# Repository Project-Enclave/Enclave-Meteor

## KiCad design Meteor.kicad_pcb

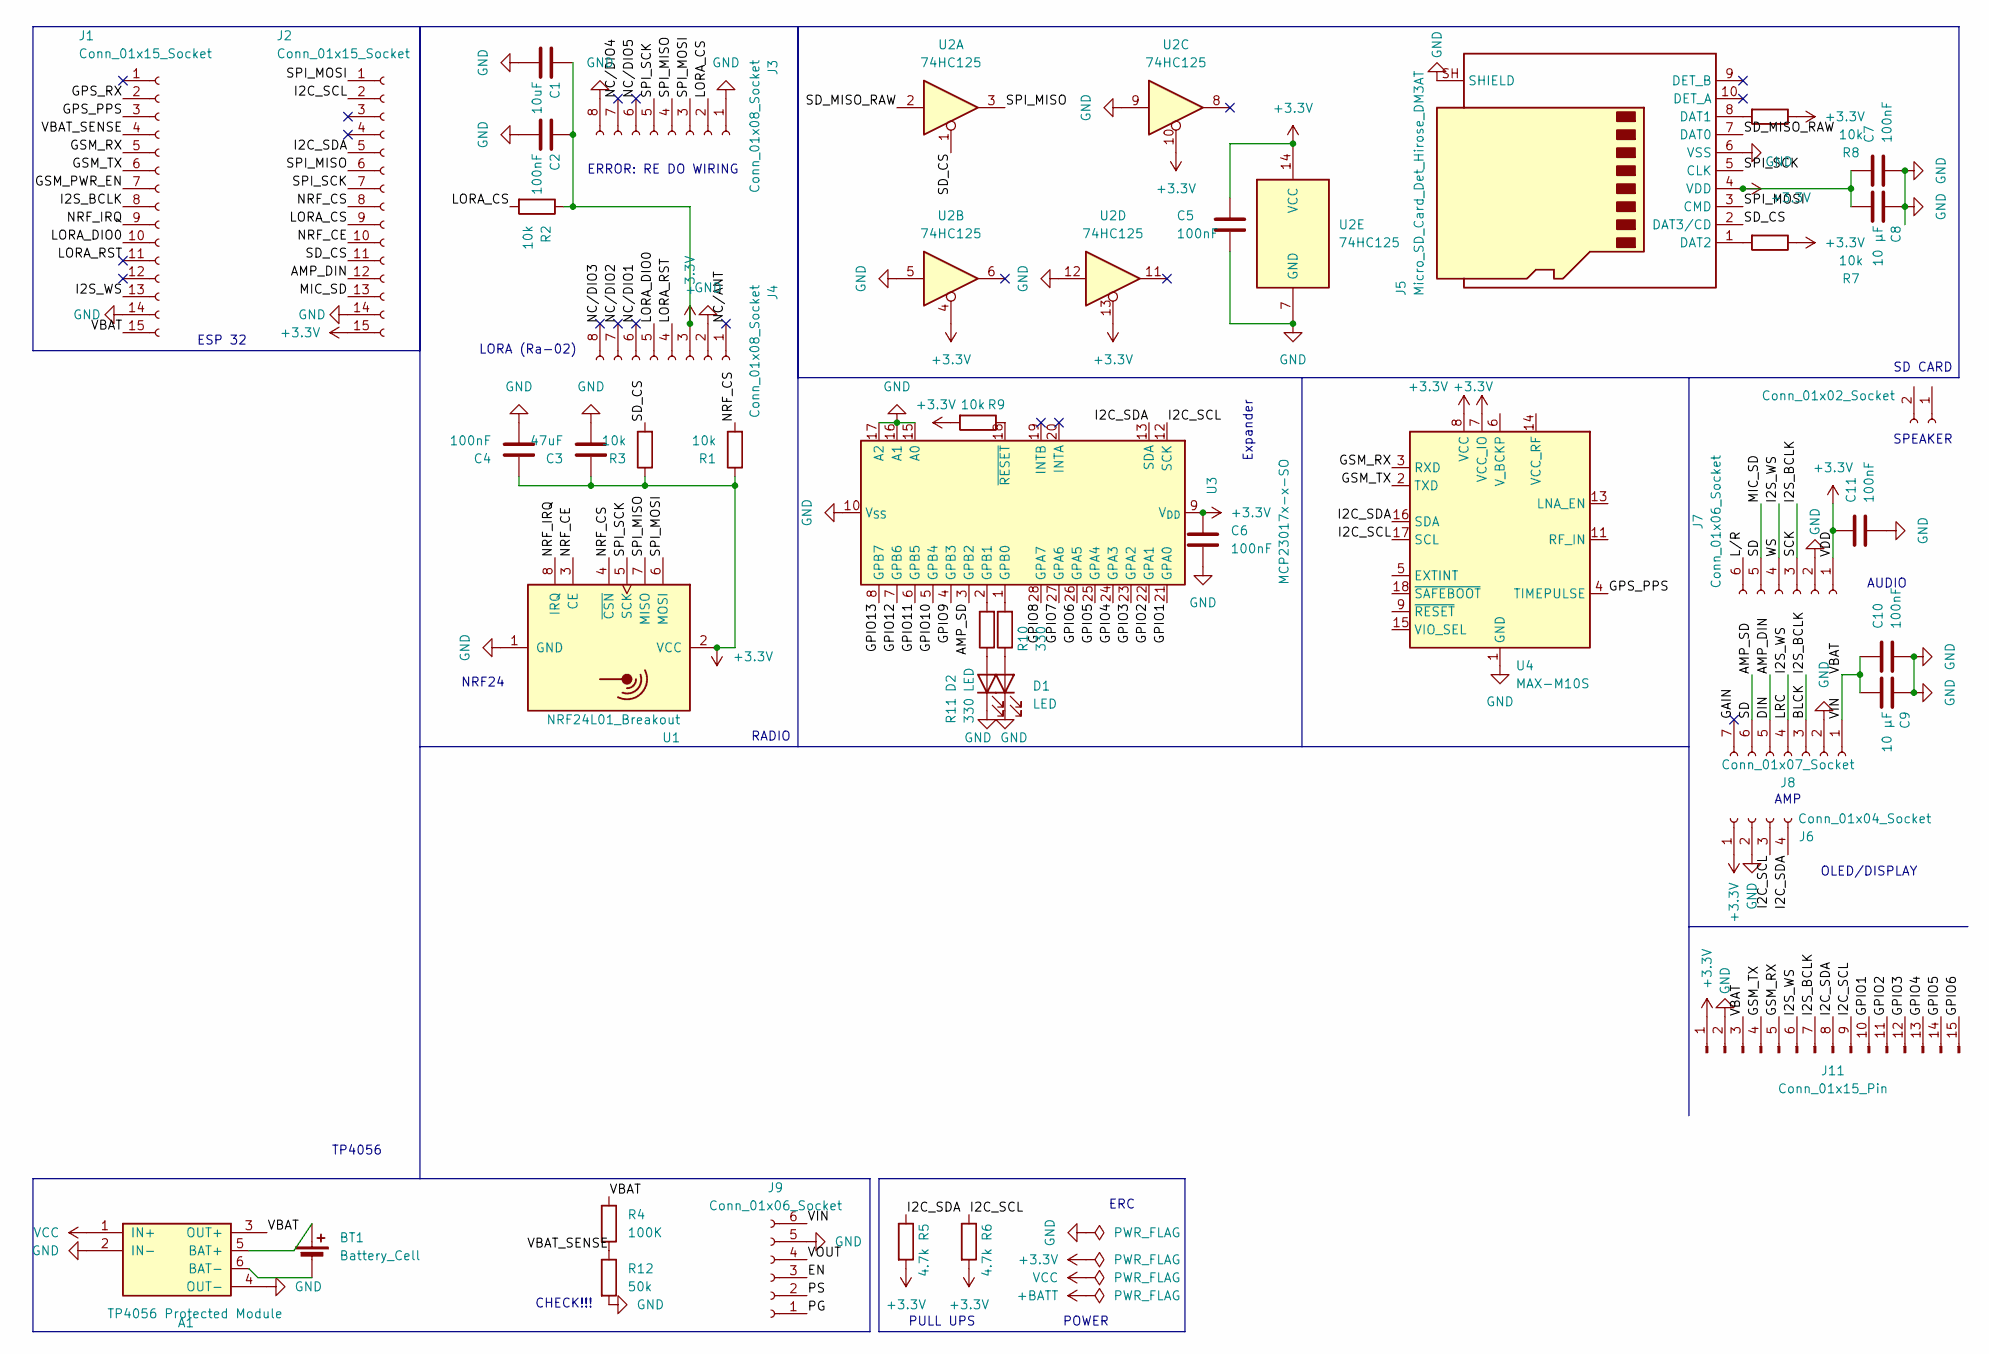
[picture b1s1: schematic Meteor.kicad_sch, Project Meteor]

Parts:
A1: TP4056 Protected Module
BT1: Battery_Cell; BatteryHolder_Keystone_1042_1x18650
C1: 10uF; C_0805_2012Metric
C2, C4, C5, C6, C7, C10, C11: 100nF; C_0805_2012Metric
C3: 47uF; C_1206_3216Metric
C8, C9: 10 µF; C_0805_2012Metric
D1, D2: LED; LED_D5.0mm_Horizontal_O3.81mm_Z15.0mm
J1, J2: Conn_01x15_Socket; PinSocket_1x15_P2.54mm_Vertical
J3, J4: Conn_01x08_Socket; PinHeader_1x08_P2.54mm_Vertical
J5: Micro_SD_Card_Det_Hirose_DM3AT; microSD_HC_Hirose_DM3AT-SF-PEJM5
J6: Conn_01x04_Socket; PinSocket_1x04_P2.54mm_Vertical
J7, J9: Conn_01x06_Socket; PinSocket_1x06_P2.54mm_Vertical
J8: Conn_01x07_Socket; PinSocket_1x07_P2.54mm_Vertical
J10: Conn_01x02_Socket; PinSocket_1x02_P2.54mm_Vertical
J11: Conn_01x15_Pin; PinHeader_1x15_P2.54mm_Vertical
R1, R2, R3, R7, R8, R9: 10k; R_0805_2012Metric
R4: 100K; R_0805_2012Metric
R5, R6: 4.7k; R_0805_2012Metric
R10, R11: 330; R_0805_2012Metric
R12: 50k; R_0805_2012Metric
U1: NRF24L01_Breakout; nRF24L01_Breakout
U2: 74HC125; DIP-14_W7.62mm
U3: MCP23017x-x-SO; SOIC-28W_7.5x17.9mm_P1.27mm
U4: MAX-M10S; ublox_MAX

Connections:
+3.3V: C1.1, C2.1, C3.1, C4.1, C5.2, C6.1, C7.1, C8.1, C11.1, J2.15, J4.3, J5.4 (VDD), J6.1, J7.1, J11.1, R1.1, R2.1, R3.1, R5.2, R6.2, R7.1, R8.1, R9.2, U1.2 (VCC), U2.4, U2.10, U2.13, U2.14 (VCC), U3.9 (V_{DD}), U4.7 (VCC_IO), U4.8 (VCC)
/AMP_DIN: J2.12, J8.5
/AMP_SD: J2.13, J7.5, J8.6, U3.3 (GPB2)
/BLCK: J1.8, J7.3, J8.3, J11.7
/EN: J9.3
/GAIN: J8.7
/GPIO1: J11.10, U3.21 (GPA0)
/GPIO2: J11.11, U3.22 (GPA1)
/GPIO3: J11.12, U3.23 (GPA2)
/GPIO4: J11.13, U3.24 (GPA3)
/GPIO5: J11.14, U3.25 (GPA4)
/GPIO6: J11.15, U3.26 (GPA5)
/GPIO7: U3.27 (GPA6)
/GPIO8: U3.28 (GPA7)
/GPIO9: U3.4 (GPB3)
/GPIO10: U3.5 (GPB4)
/GPIO11: U3.6 (GPB5)
/GPIO12: U3.7 (GPB6)
/GPIO13: U3.8 (GPB7)
/GPS_PPS: J1.3, U4.4 (TIMEPULSE)
/GPS_RX: J1.2
/GSM_PWR_EN: J1.7
/GSM_RX: J1.5, J11.5, U4.3 (RXD)
/GSM_TX: J1.6, J11.4, U4.2 (TXD)
/I2C_SCL: J2.2, J6.3, J11.9, R6.1, U3.12 (SCK), U4.17 (SCL)
/I2C_SDA: J2.5, J6.4, J11.8, R5.1, U3.13 (SDA), U4.16 (SDA)
/I2S_WS: J1.13, J7.4, J8.4, J11.6
/LORA_CS: J2.9, J3.2, R2.2
/LORA_DIO0: J1.10, J4.5
/LORA_RST: J1.11, J4.4
/L/R: J7.6
/NC/ANT: J4.1
/NC/DIO1: J4.6
/NC/DIO2: J4.7
/NC/DIO3: J4.8
/NC/DIO4: J3.7
/NC/DIO5: J3.6
/NRF_CE: J2.10, U1.3 (CE)
/NRF_CS: J2.8, R1.2, U1.4 (~CSN)
/NRF_IRQ: J1.9, U1.8 (IRQ)
/PG: J9.1
/PS: J9.2
/SD_CS: J2.11, J5.2 (DAT3/CD), R3.2, U2.1
/SD_MISO_RAW: J5.7 (DAT0), U2.2
/SPI_MISO: J2.6, J3.4, U1.7 (MISO), U2.3
/SPI_MOSI: J2.1, J3.3, J5.3 (CMD), U1.6 (MOSI)
/SPI_SCK: J2.7, J3.5, J5.5 (CLK), U1.5 (SCK)
/VBAT: A1.3 (OUT+), C9.1, C10.1, J1.15, J8.1, J9.6, J11.3, R4.1
/VBAT_SENSE: J1.4, R4.2, R12.1
/VOUT: J9.4
GND: A1.2 (IN-), A1.4 (OUT-), C1.2, C2.2, C3.2, C4.2, C5.1, C6.2, C7.2, C8.2, C9.2, C10.2, C11.2, D1.1 (K), D2.1 (K), J1.14, J2.14, J3.1, J3.8, J4.2, J5.6 (VSS), J5.SH (SHIELD), J6.2, J7.2, J8.2, J9.5, J11.2, R12.2, U1.1 (GND), U2.5, U2.7 (GND), U2.9, U2.12, U3.10 (V_{SS}), U3.15 (A0), U3.16 (A1), U3.17 (A2), U4.1 (GND), U4.10 (GND), U4.12 (GND)
unnamed: A1.5 (BAT+), BT1.1 (+)
unnamed: A1.6 (BAT-), BT1.2 (-)
unnamed: D1.2 (A), R10.1
unnamed: D2.2 (A), R11.1
unnamed: J5.8 (DAT1), R8.2
unnamed: J5.1 (DAT2), R7.2
unnamed: R10.2, U3.1 (GPB0)
unnamed: R11.2, U3.2 (GPB1)
unnamed: R9.1, U3.18 (~RESET)
VCC: A1.1 (IN+)

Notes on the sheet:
SD CARD
TP4056
CHECK!!!
RADIO
ERC
ERROR: RE DO WIRING
LORA (Ra-02)
OLED/DISPLAY
PULL UPS
Expander
POWER
AUDIO
AMP
ESP 32
NRF24
SPEAKER

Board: 2 copper layers, 42 parts (0 on the bottom side), 39 nets, no tracks yet.

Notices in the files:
Meteor.kicad_sch:
This is under the GNU 3.0 License
